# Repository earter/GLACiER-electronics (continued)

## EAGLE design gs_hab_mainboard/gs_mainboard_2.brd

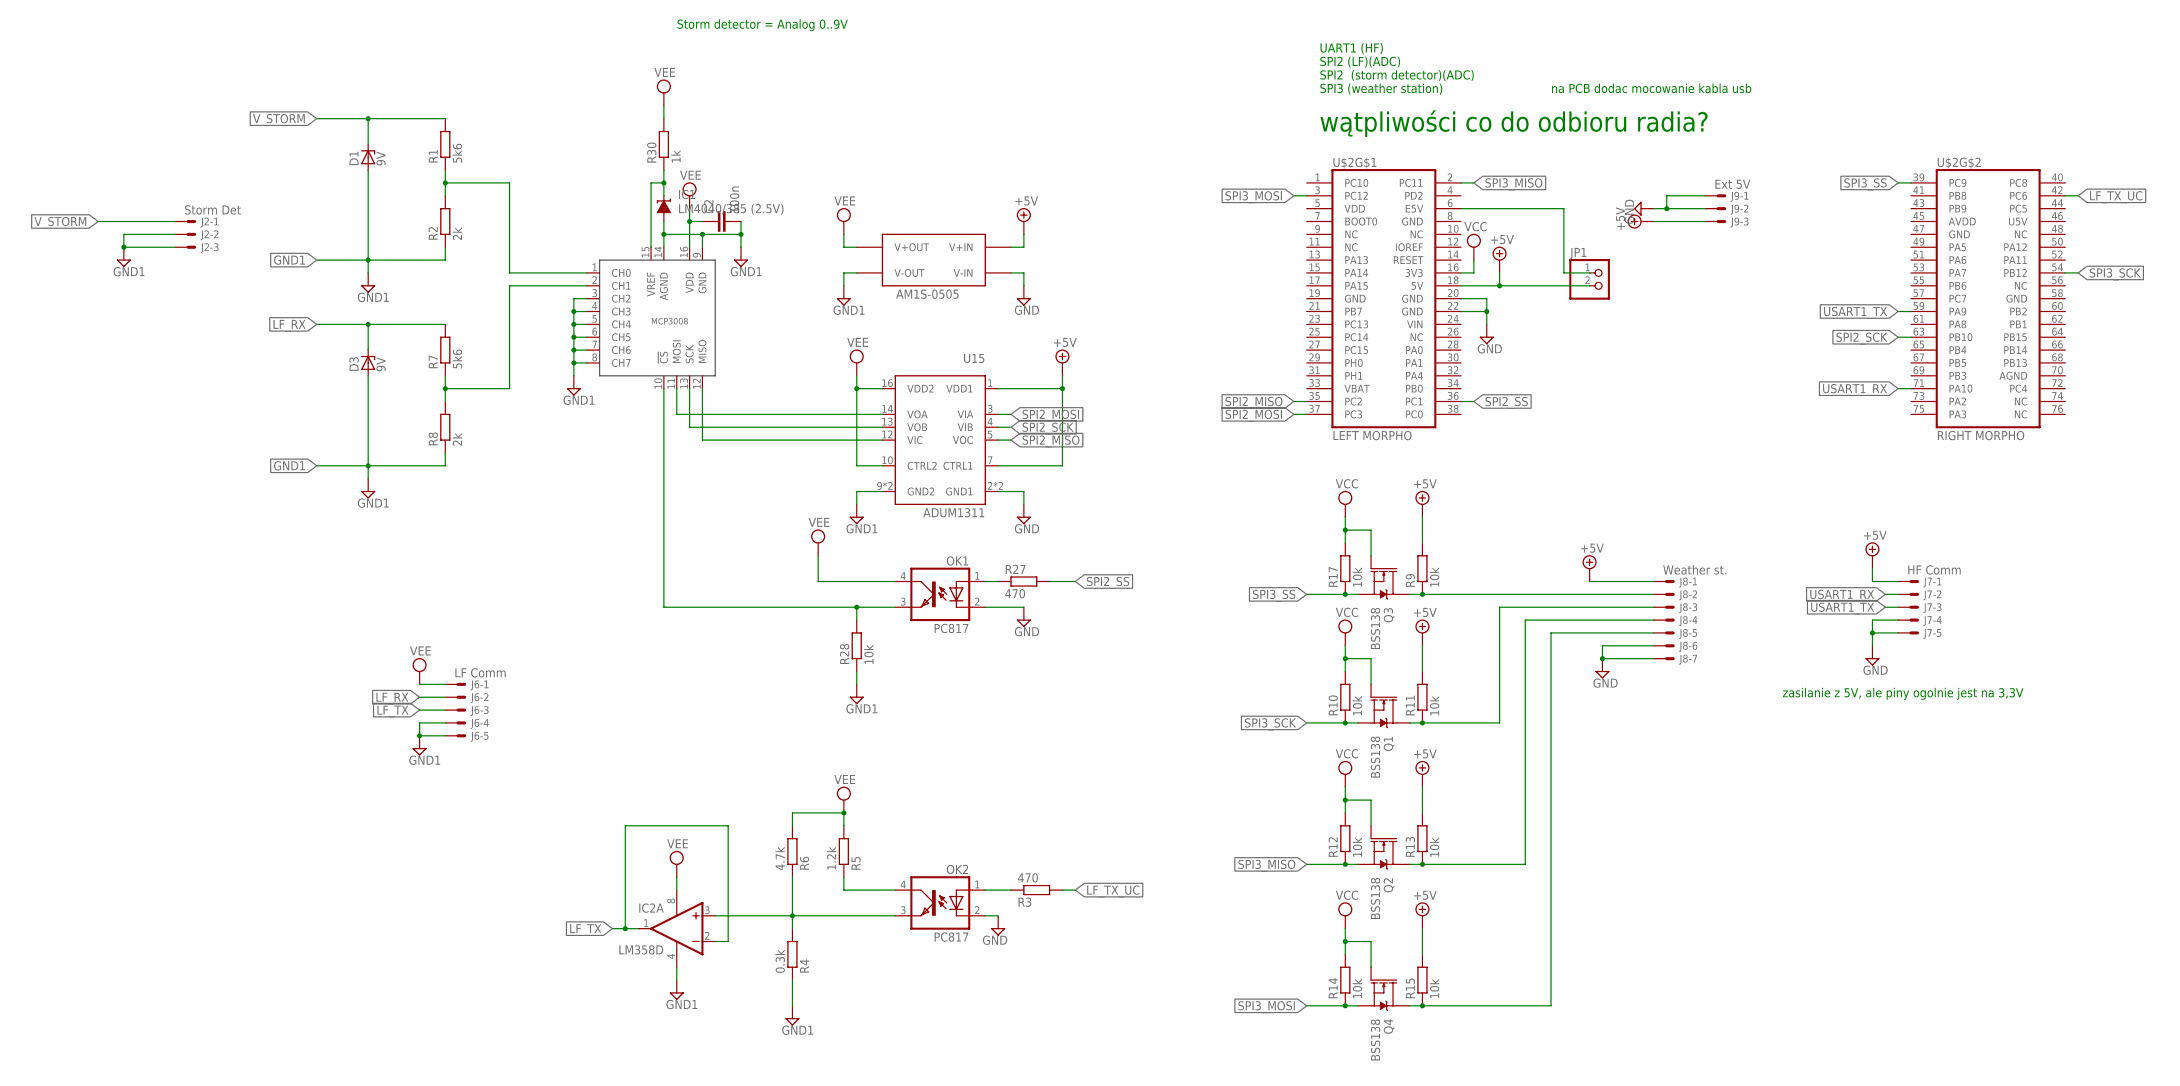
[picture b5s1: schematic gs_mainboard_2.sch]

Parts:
C2: 100n; C0805
D1, D3: 9V; SOT23
IC1: LM4040/385 (2.5V); DBZ_R-PDSO-G3
IC2: LM358D; SO08
J2: Storm Det; 7395-03
J6: LF Comm; 7395-05
J7: HF Comm; 7395-05
J8: Weather st.; 7395-07
J9: Ext 5V; 7395-03
JP1: PINHD-1X2; 1X02
OK1, OK2: PC817; DIL04
Q1, Q2, Q3, Q4: BSS138; SOT23-3
R1, R7: 5k6; R0805
R2, R8: 2k; R0805
R3, R27: 470; M0805
R4: 0.3k; M0805
R5: 1.2k; M0805
R6: 4.7k; M0805
R9, R10, R11, R12, R13, R14, R15, R17, R28: 10k; M0805
R30: 1k; M0805
U13: MCP3008SL; SO16
U15: ADUM1311; SOIC-16W
U$2: NUCLEO_F411RE_MORPHO; MORPHO_HEADERS
U$14: AM1S-0505; SIP4

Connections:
+5V: J7.1, J8.1, J9.3, JP1.2, R9.2, R11.2, R13.2, R15.2, U15.1 (VDD1), U15.7 (CTRL1), U$2.18 (5V), U$14.P$2 (V+IN)
AGND: U$2.70 (AGND)
AVDD: U$2.45 (AVDD)
E5V: JP1.1, U$2.6 (E5V)
GND: J7.4, J7.5, J8.6, J8.7, J9.1, J9.2, OK1.2 (C), OK2.2 (C), U15.2 (GND1), U15.8 (GND1), U$2.8 (GND), U$2.19 (GND), U$2.20 (GND), U$2.22 (GND), U$2.47 (GND), U$2.58 (GND), U$14.P$1 (V-IN)
GND1: C2.2, D1.1 (A), D3.1 (A), IC1.2 (A), IC2.4 (V-), J2.2, J2.3, J6.4, J6.5, R2.1, R4.1, R8.1, R28.1, U13.3 (CH2), U13.4 (CH3), U13.5 (CH4), U13.6 (CH5), U13.7 (CH6), U13.8 (CH7), U13.9 (GND), U13.14 (AGND), U15.9 (GND2), U15.15 (GND2), U$14.P$3 (V-OUT)
LF_RX: D3.3 (C), J6.2, R7.2
LF_TX: IC2.1 (OUT), IC2.2 (-IN), J6.3
LF_TX1: IC2.3 (+IN), OK2.3 (EMIT), R4.2, R6.1
LF_TX_UC: R3.2, U$2.42 (PC6)
unnamed: R7.1, R8.2, U13.2 (CH1)
unnamed: OK2.1 (A), R3.1
unnamed: OK2.4 (COL), R5.1
unnamed: R1.1, R2.2, U13.1 (CH0)
unnamed: IC1.1 (C), R30.1, U13.15 (VREF)
unnamed: OK1.1 (A), R27.1
unnamed: OK1.3 (EMIT), R28.2, U13.10 (!CS)
unnamed: U13.11 (MOSI), U15.14 (VOA)
unnamed: U13.13 (SCK), U15.13 (VOB)
unnamed: U13.12 (MISO), U15.12 (VIC)
SPI2_MISO: U15.5 (VOC), U$2.35 (PC2)
SPI2_MOSI: U15.3 (VIA), U$2.37 (PC3)
SPI2_SCK: U15.4 (VIB), U$2.63 (PB10)
SPI2_SS: R27.2, U$2.36 (PC1)
SPI3_MISO: Q2.2 (S), R12.1, U$2.2 (PC11)
SPI3_MISO_EXT: J8.4, Q2.3 (D), R13.1
SPI3_MOSI: Q4.2 (S), R14.1, U$2.3 (PC12)
SPI3_MOSI_EXT: J8.5, Q4.3 (D), R15.1
SPI3_SCK: Q1.2 (S), R10.1, U$2.54 (PB12)
SPI3_SCK_EXT: J8.3, Q1.3 (D), R11.1
SPI3_SS: Q3.2 (S), R17.1, U$2.39 (PC9)
SPI3_SS_EXT: J8.2, Q3.3 (D), R9.1
U5V: U$2.46 (U5V)
USART1_RX: J7.2, U$2.71 (PA10)
USART1_TX: J7.3, U$2.59 (PA9)
VBAT: U$2.33 (VBAT)
VCC: Q1.1 (G), Q2.1 (G), Q3.1 (G), Q4.1 (G), R10.2, R12.2, R14.2, R17.2, U$2.16 (3V3)
VDD: U$2.5 (VDD)
VEE: C2.1, IC2.8 (V+), J6.1, OK1.4 (COL), R5.2, R6.2, R30.2, U13.16 (VDD), U15.10 (CTRL2), U15.16 (VDD2), U$14.P$4 (V+OUT)
VIN: U$2.24 (VIN)
V_STORM: D1.3 (C), J2.1, R1.2

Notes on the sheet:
UART1 (HF) SPI2 (LF)(ADC) SPI2 (storm detector)(ADC) SPI3 (weather station)
na PCB dodac mocowanie kabla usb
zasilanie z 5V, ale piny ogolnie jest na 3,3V
Storm detector = Analog 0..9V
wątpliwości co do odbioru radia?

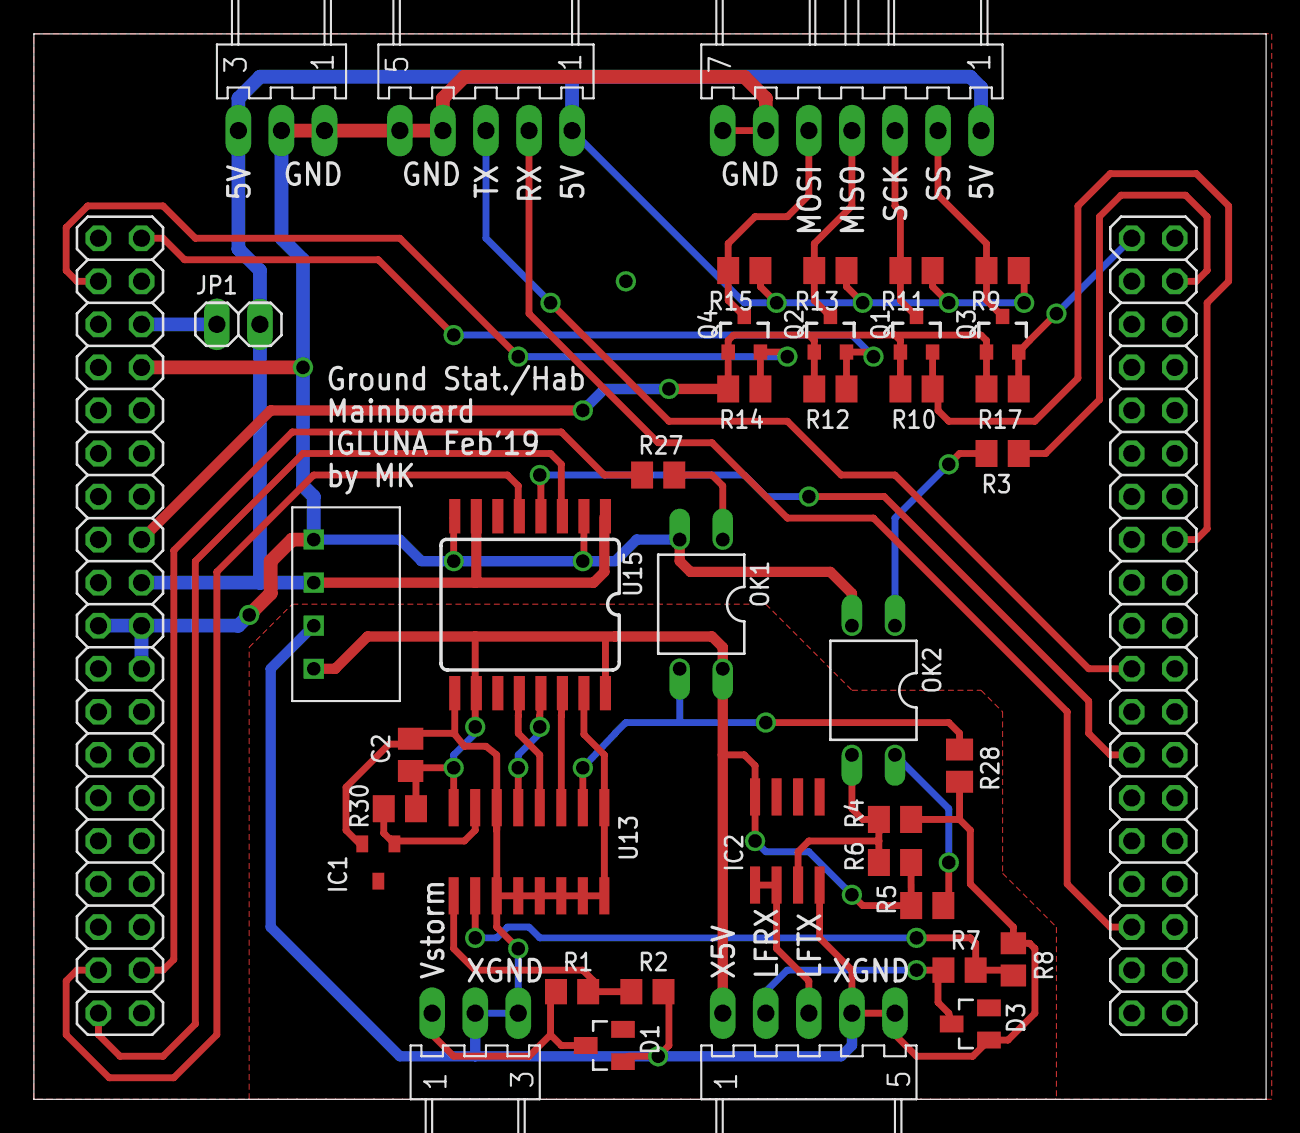
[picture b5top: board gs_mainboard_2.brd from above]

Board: 2 copper layers, 72.7 x 62.9 mm, 40 parts (0 on the bottom side), 35 nets.

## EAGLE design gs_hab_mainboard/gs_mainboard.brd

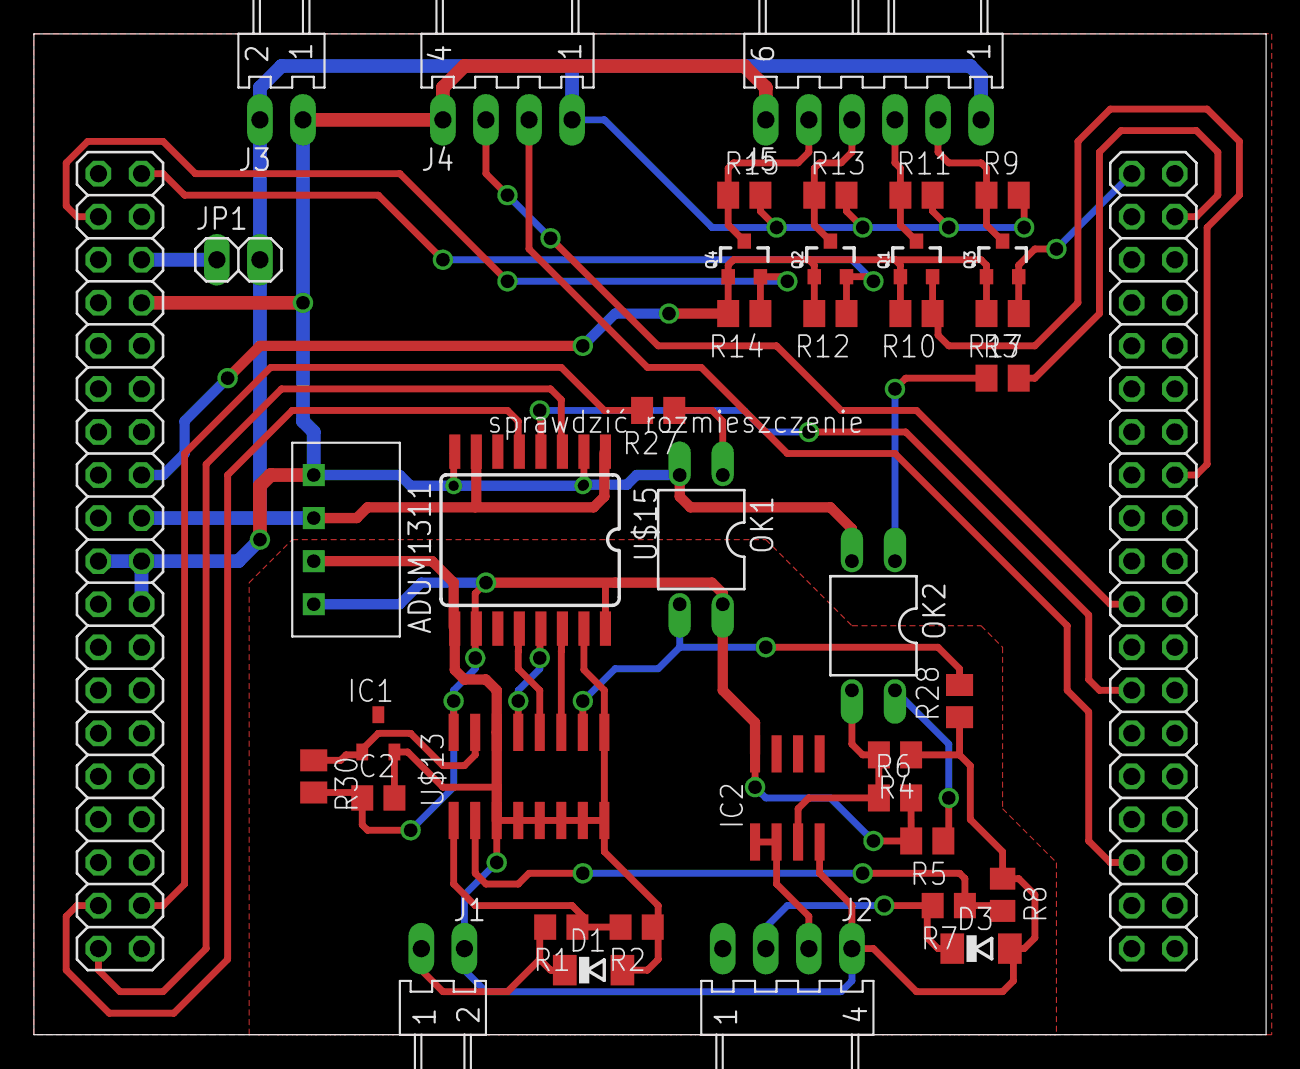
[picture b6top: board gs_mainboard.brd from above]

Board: 2 copper layers, 72.7 x 59.0 mm, 40 parts (0 on the bottom side), 35 nets.

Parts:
C2: 100n; C0805
D1, D3: 9V; SOD80C
IC1: LM4040/385 (2.5V); DBZ_R-PDSO-G3
IC2: LM358D; SO08
J1: Storm Det; 7395-02
J2: LF Comm; 7395-04
J3: EXT_SUPP; 7395-02
J4: HF Comm (UART); 7395-04
J5: Weather station (SPI); 7395-06
JP1: 1X02
OK1, OK2: PC817; DIL04
Q1, Q2, Q3, Q4: BSS138; SOT23-3
R1, R7: 5k6; R0805
R2, R8: 2k; R0805
R3, R27: 470; M0805
R4: 0.3k; M0805
R5: 1.2k; M0805
R6: 4.7k; M0805
R9, R10, R11, R12, R13, R14, R15, R17, R28: 10k; M0805
R30: 1k; M0805
U$2: NUCLEO_F411RE_MORPHO; MORPHO_HEADERS
U$13: MCP3008SL; SO16
U$14: AM1S-0505; SIP4
U$15: ADUM1311; SOIC-16W

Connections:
+5V: J3.2, J4.1, J5.1, JP1.2, R9.2, R11.2, R13.2, R15.2, U$2.18, U$14.P$2, U$15.1, U$15.7
E5V: JP1.1, U$2.6
GND: J3.1, J4.4, J5.6, OK1.2, OK2.2, U$2.8, U$2.19, U$2.20, U$2.22, U$2.47, U$2.58, U$14.P$1, U$15.2, U$15.8
GND1: C2.2, D1.A, D3.A, IC1.2, IC2.4, J1.2, J2.4, R2.1, R4.1, R8.1, R28.1, U$13.3, U$13.4, U$13.5, U$13.6, U$13.7, U$13.8, U$13.9, U$13.14, U$14.P$3, U$15.9, U$15.15
LF_RX: D3.C, J2.2, R7.2
LF_TX: IC2.1, IC2.2, J2.3
LF_TX1: IC2.3, OK2.3, R4.2, R6.1
LF_TX_UC: R3.2, U$2.42
unnamed: R7.1, R8.2, U$13.2
unnamed: OK2.1, R3.1
unnamed: OK2.4, R5.1
unnamed: R1.1, R2.2, U$13.1
unnamed: IC1.1, R30.1, U$13.15
unnamed: OK1.1, R27.1
unnamed: OK1.3, R28.2, U$13.10
unnamed: U$13.11, U$15.14
unnamed: U$13.13, U$15.13
unnamed: U$13.12, U$15.12
SPI2_MISO: U$2.35, U$15.5
SPI2_MOSI: U$2.37, U$15.3
SPI2_SCK: U$2.63, U$15.4
SPI2_SS: R27.2, U$2.36
SPI3_MISO: Q2.2, R12.1, U$2.2
SPI3_MISO_EXT: J5.3, Q1.3, R11.1
SPI3_MOSI: Q4.2, R14.1, U$2.3
SPI3_MOSI_EXT: J5.2, Q3.3, R9.1
SPI3_SCK: Q1.2, R10.1, U$2.54
SPI3_SS: Q3.2, R17.1, U$2.39
SPI3_SS_EXT: J5.4, Q2.3, R13.1
SPI3_SS_EXT1: J5.5, Q4.3, R15.1
USART1_RX: J4.2, U$2.71
USART1_TX: J4.3, U$2.59
VCC: Q1.1, Q2.1, Q3.1, Q4.1, R10.2, R12.2, R14.2, R17.2, U$2.16
VEE: C2.1, IC2.8, OK1.4, R5.2, R6.2, R30.2, U$13.16, U$14.P$4, U$15.10, U$15.16
V_STORM: D1.C, J1.1, R1.2

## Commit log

2019-01-29 dodane LBR shieldow i mainboardy (niegotowe)
2019-02-11 minor updates
2019-02-14 some libs added/corrected
2019-02-15 added boards for astronaut
2019-02-17 added hf comm schematic
2019-02-19 Nowe schematy i pcb
2019-02-20 new_versions
2019-02-20 added lib current sensor
2019-02-20 newest versions
2019-02-21 New_version
2019-02-23 added gs_mainboard layout
2019-02-23 PMS v2
2019-02-24 kolejan wersja
2019-02-27 v1 poprawki
2019-03-01 modified boards, repo ordered into folders
2019-03-02 updated lib, corrected boards (after printing)
2019-03-02 v4 PMS i lekka poprawka DWM
2019-03-02 v4_poprawione
2019-03-02 Po poprawkach
2019-03-02 ostatnie poprawki
2019-03-04 new voltage stabilizer
2019-03-04 update relay
2019-03-06 verified, ready to production
2019-03-06 corrected pms
2019-03-06 napisy
2019-03-06 final, after another review
2019-03-07 really final projects, added gerber files
2019-03-08 corrected gerbers, cleaned schematics, added documnetation
2019-03-09 Wygenerwone gerbery
2019-03-09 Lekkie zmiany w rozmieszczeniu nazewnictwa
2019-03-09 Commity gerberków
2019-03-10 corrected gerbers
2019-05-22 Created using Colaboratory
2019-08-21 Final version
